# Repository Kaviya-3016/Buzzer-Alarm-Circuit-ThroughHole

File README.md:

# 🔔 Simple Buzzer Alarm Using Through Hole

This project is a simple electronics circuit designed using **EAGLE PCB Design Tool** to create a single-layer through-hole PCB for a buzzer-based alarm system using the **NE555 Timer IC**.

---

## 📘 Overview

The buzzer alarm circuit generates a sound alert using a speaker whenever powered. It uses a 555 timer in astable mode to generate pulses that drive the buzzer. This project is ideal for beginners to learn the basics of PCB design and component interfacing.

---

## 🧩 Components Used (BOM)

| Qty | Value   | Device        | Package      | Designator | Description                |
| --- | ------- | ------------- | ------------ | ---------- | -------------------------- |
| 1   | 0.1uF   | Capacitor     | C025-024X070 | C1         | Capacitor, American symbol |
| 2   | 100uF   | CPOL-USE5     | E5-10.5      | C3, C4     | Polarized Capacitor        |
| 1   | 10uF    | CPOL-USE2     | E2-5         | C2         | Polarized Capacitor        |
| 1   | 15k     | Resistor      | 0204/5       | R2         | Resistor                   |
| 1   | 5.6k    | Resistor      | 0204/5       | R3         | Resistor                   |
| 1   | 1k      | Potentiometer | PT-10        | R1         | Variable Resistor          |
| 1   | NE555N  | IC            | DIL08        | IC1        | 555 Timer IC               |
| 1   | KSS1201 | Speaker       | KSS1201      | SP1        | Alarm/Buzzer               |
| 1   | AB9V    | Battery Clip  | AB9V         | G1         | 9V Battery Clip            |

---

## 🔧 Software Used

* **Autodesk EAGLE 7.5.0 Light**
  Used to design both the schematic and PCB layout of the circuit.

---

## 🖥️ Files Included

* 📄 Schematic Design (`.sch`)
* 📄 Board Layout (`.brd`)
* 📄 BOM (Bill of Materials) text file
* 📷 Schematic and PCB layout images

---

## 📐 PCB Details

* **Layer**: Single Layer
* **Design**: Through-Hole Components
* **Board Dimensions**: 55.88mm × 43.17mm
* **IC Used**: NE555 Timer
* **PCB Features**:

  * Compact layout
  * Clear component labeling
  * Manually routed traces

---

## ⚙️ Working Principle

* The NE555 Timer is configured in **astable mode**.
* It continuously switches between HIGH and LOW states, generating square wave pulses.
* These pulses drive the buzzer (SP1) to produce sound.
* You can control the tone/frequency by adjusting the **potentiometer (R1)**.

---

## ✅ Advantages

* Simple and beginner-friendly
* Easy to assemble using through-hole components
* Reusable design for various 555 timer-based applications

---

## ❌ Limitations

* Fixed buzzer tone (unless modified with different resistor/capacitor values)
* Not suitable for high-frequency or programmable alerts

---

## 📸 Previews

### Schematic

### PCB Layout

### BOM

---

## 💡 Future Improvements

* Use a programmable microcontroller for custom alarm patterns
* Add motion sensor or light sensor to activate buzzer conditionally
* Convert it into a wearable or enclosure-ready module

---

## 👩‍💻 Author

**Kaviya Murugan**
PCB Design Enthusiast | ECE Engineer | AI Intern @ Infosys Springboard

Feel free to ⭐ the repo or fork it for your own experiments!

---

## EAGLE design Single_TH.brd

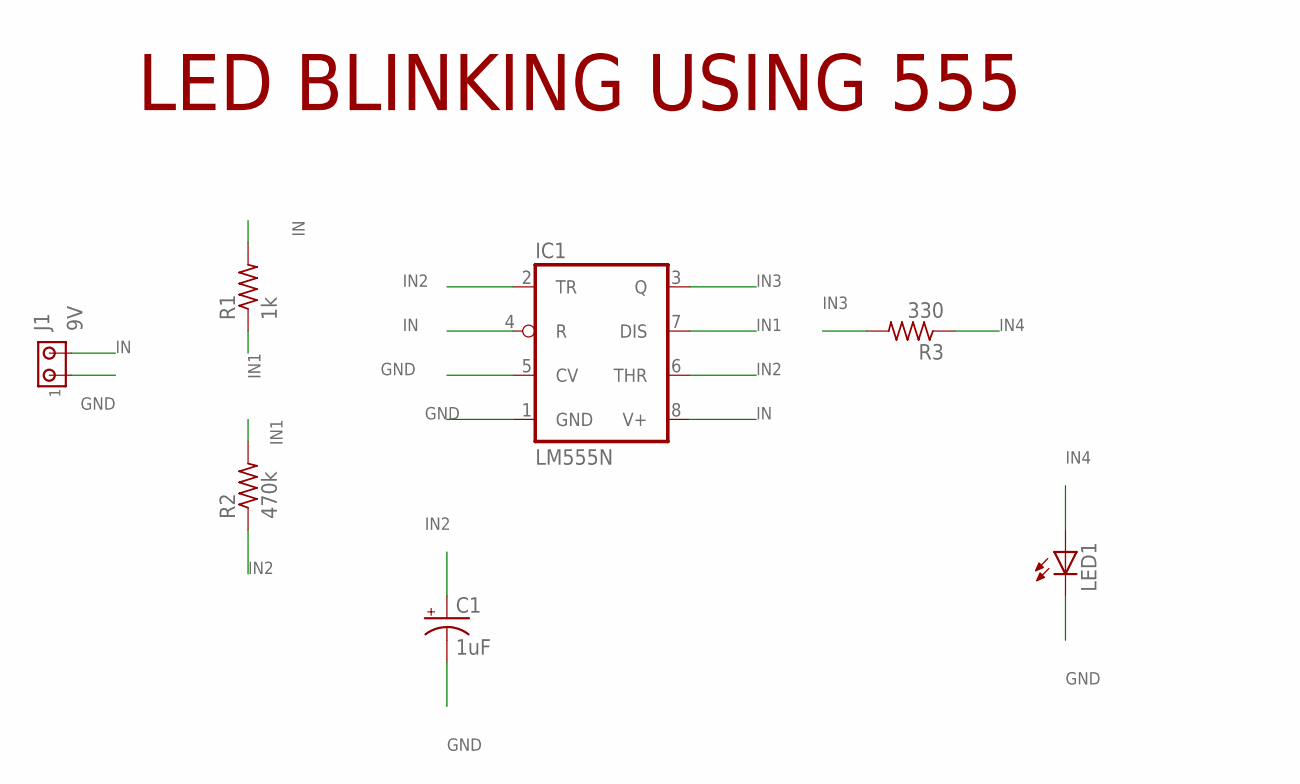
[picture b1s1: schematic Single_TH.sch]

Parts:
C1: 1uF; E2,5-7
IC1: LM555N; DIL08
J1: 9V; 1X2MTA
LED1: LED5MM
R1: 1k; 0204/5
R2: 470k; 0204/5
R3: 330; 0204/5

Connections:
GND: C1.-, IC1.1 (GND), IC1.5 (CV), J1.1, LED1.K (C)
IN: IC1.4 (R), IC1.8 (V+), J1.2, R1.2
IN1: IC1.7 (DIS), R1.1, R2.2
IN2: C1.+, IC1.2 (TR), IC1.6 (THR), R2.1
IN3: IC1.3 (Q), R3.2
IN4: LED1.A, R3.1

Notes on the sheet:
LED BLINKING USING 555

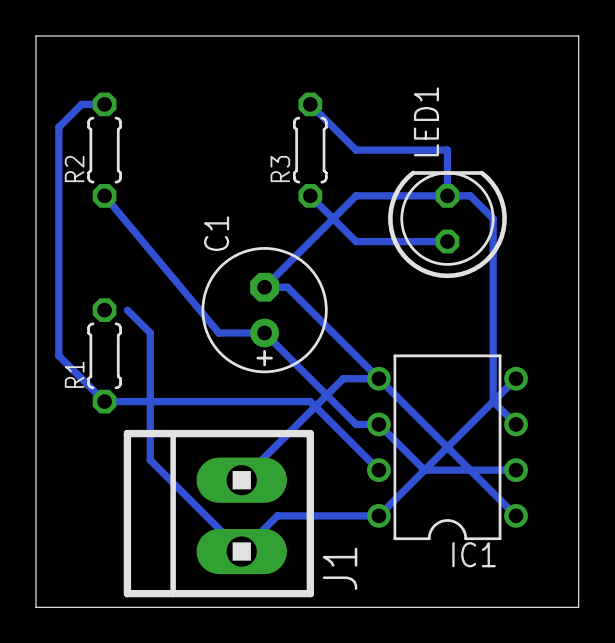
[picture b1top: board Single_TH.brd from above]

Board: 2 copper layers, 30.1 x 31.7 mm, 7 parts (0 on the bottom side), 6 nets.
